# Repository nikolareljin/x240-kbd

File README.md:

# x240-kbd

A standalone USB keyboard with touchpad **and TrackPoint**, built from a ThinkPad X240
keyboard assembly (FRU 0C44020) and its Synaptics ClickPad, driven by a Raspberry Pi Pico
(RP2040) running QMK.

Works on **any OS without drivers** — it enumerates as a standard USB HID composite device
(keyboard + mouse + media keys).

> **Project status: design, not yet built.** The matrix pinout is unverified until the
> probing step runs on real hardware, and the TrackPoint route (via the ClickPad's PS/2
> pass-through) is the expected architecture, confirmed by the same step. Everything else
> here is designed to survive either answer. Track progress in the
> [issues](https://github.com/nikolareljin/x240-kbd/issues) — nine milestones from
> documentation to release.

---

## Features

- Full 84-key ThinkPad X240 layout (QWERTY, US)
- Synaptics ClickPad — cursor, left/right click zones
- **TrackPoint** — via the ClickPad's pass-through port, decoded in firmware
- FN layer with the ThinkPad media/system keys; FN Lock (FN + Esc)
- Keyboard backlight, 5 levels (backlit keyboard variants; no breathing — software PWM)
- Power button with a 500 ms long-press guard → OS power/sleep
- Touchpad indicator LED
- N-Key Rollover
- Micro-USB; documented USB-C upgrade
- Two enclosure routes: **3D-printed** (split case) or **hand-made with no printer**
- Two electronics revisions: **Rev A perfboard** and **Rev B KiCad PCB**, same firmware

---

## Hardware at a glance

| Component | Detail |
|---|---|
| Controller | Raspberry Pi Pico, RP2040, 26 GPIO |
| Keyboard | X240 0C44020, 40-pin 0.5 mm FPC; matrix size **measured by probing** |
| Sense expansion | 3 × 74HC165 shift registers — 24 sense lines on 3 GPIO |
| Touchpad + TrackPoint | Synaptics ClickPad, PS/2 on GP21/GP22 (RP2040 PIO driver) |
| Backlight | LED strip via 2N7002/BS170 MOSFET on GP26 |
| Power button | GP27, active LOW |
| USB | Micro-USB; USB-C via the Pico's TP1/TP2/TP3 pads |
| Enclosure | Printed split case, or the original X240 base cover, laser-cut plates, a Hammond console or wood |

Why a shift register: the closest documented ThinkPad keyboard of this era needs 26 matrix
lines — every GPIO the Pico has. [`docs/hardware/gpio-budget.md`](docs/hardware/gpio-budget.md).

### Cost

| Build | All-in (USD, Aug 2026) |
|---|---|
| Rev A + your own printer | **$90–130** |
| Rev A + reused X240 base cover, no printer | **$110–150** |
| Rev B PCB | add $25–35 |

The donor keyboard and palmrest are most of it. Full tiers and part links:
[`docs/hardware/bom-and-cost.md`](docs/hardware/bom-and-cost.md).

---

## Repository structure

```
x240-kbd/
├── firmware/qmk/keyboards/x240_pico/   QMK keyboard definition (corrected in milestone M4)
├── hardware/pinout/                     FPC pin maps — filled by probing
├── hardware/wiring/                     GPIO table (the single authoritative copy) and schematics
├── hardware/pcb/                        Rev B KiCad project (milestone M7)
├── tools/matrix_probe/                  CircuitPython matrix discovery
├── tools/ps2_sniffer/                   CircuitPython PS/2 + Synaptics sniffer
├── cad/                                 OpenSCAD: split case and small printed parts
└── docs/                                The documentation site (GitHub Pages from /docs)
    ├── hardware/                        components, BOM & cost, GPIO budget, sense chain, TrackPoint, backlight, PCB
    ├── firmware/                        architecture, QMK configuration, pointing stack
    ├── enclosure/                       printed, hand-made, integration, durability, presentation
    ├── references.md · glossary.md
    └── images/
```

---

## Quick start

Everything runs through one entry point, `./dev` (verbs from the workspace-wide
[script-helpers](https://github.com/nikolareljin/script-helpers) template; toolchains in
Docker, so the host needs only `docker`, `git` and `python3`):

```bash
./dev install            # submodules, docker images, a shallow qmk_firmware checkout
./dev build [firmware|docs|tools|cad|pcb|all]
./dev test               # host pytest for the tools, link check, shellcheck
./dev preflight          # everything CI runs: test + build all
./dev deploy             # copy the UF2 to the Pico's RPI-RP2 drive  (alias: ./flash)
./dev deploy matrix_probe   # copy a probing tool to CIRCUITPY        (alias: ./probe <tool>)
./dev devices            # RPI-RP2 / CIRCUITPY mounts and serial ports
./dev logs               # qmk console — the firmware's debug output
```

Shims `./build`, `./test`, `./flash`, `./probe`, `./site` wrap the same verbs. Artifacts
land in `out/`. The Docker images and the `qmk_firmware` commit are **pinned by digest**
in `scripts/toolchain.env` (`scripts/pull_toolchain.sh` pulls, saves or refreshes them),
so today's build can be repeated later. CI (`.github/workflows/ci.yml`, via
[ci-helpers](https://github.com/nikolareljin/ci-helpers)) runs `./dev test` and
`./dev build all` on every push and PR.

1. **Read the component reference and buy parts** —
   [`docs/hardware/components.md`](docs/hardware/components.md),
   [`docs/hardware/bom-and-cost.md`](docs/hardware/bom-and-cost.md).
2. **Probe the FPC pinouts — mandatory first step.** Flash CircuitPython, `./probe
   matrix_probe`, then `./probe ps2_sniffer`, following
   [`hardware/pinout/probing_procedure.md`](hardware/pinout/probing_procedure.md). Do not
   wire the Pico to anything before this is done.
3. **Build the Rev A adapter** — [`ASSEMBLY.md`](ASSEMBLY.md) Phase 2, using
   [`hardware/wiring/wiring_diagram.md`](hardware/wiring/wiring_diagram.md).
4. **Build and flash firmware** — `./dev build` then `./dev deploy` (hold BOOTSEL while
   plugging in). Without `./dev`: copy `firmware/qmk/keyboards/x240_pico` into a QMK
   checkout and `qmk compile -kb x240_pico -km default`. The firmware **builds** (custom
   74HC165 matrix, PIO PS/2 host, Synaptics + TrackPoint decoding); the key map is a
   placeholder until probing (#38). [`docs/firmware/qmk-configuration.md`](docs/firmware/qmk-configuration.md).
5. **Choose an enclosure** — printed:
   [`docs/enclosure/printed.md`](docs/enclosure/printed.md); no printer:
   [`docs/enclosure/handmade.md`](docs/enclosure/handmade.md).
6. **Close it up** — [`docs/enclosure/presentation.md`](docs/enclosure/presentation.md)
   has the assembly order.

---

## FN key map

| FN + | Action | | FN + | Action |
|---|---|---|---|---|
| F1 | Mute | | F9 | Settings |
| F2 | Volume down | | F10 | Bluetooth |
| F3 | Volume up | | F11 | **Backlight step** |
| F4 | Mic mute (F20) | | F12 | Print Screen |
| F5 | Brightness down | | PgUp / PgDn | Home / End |
| F6 | Brightness up | | Left / Right | Previous / next track |
| F7 | External display | | Esc | **FN Lock** |
| F8 | Wireless toggle | | | |

---

## USB-C upgrade (optional)

Wire a USB-C female breakout (one with 5.1 kΩ CC pull-downs) to the pads on the Pico's
underside:

| Pico pad | Signal | Breakout |
|---|---|---|
| **TP1** | **GND** | GND |
| **TP2** | **USB D−** | D− |
| **TP3** | **USB D+** | D+ |
| VBUS (pin 40) | 5 V | VBUS |

Set `usb_c = true` in `cad/bottom_case.scad` for the USB-C cutout. No firmware change.

> The illustration [`docs/images/usb_c_wiring.png`](docs/images/usb_c_wiring.png) is
> decorative; its pad labels predate this table and are **not** the wiring reference.
> Source: [Pico datasheet, test points](https://datasheets.raspberrypi.com/pico/pico-datasheet.pdf).

Alternatively use a **Pimoroni Pico LiPo** (USB-C native, same pinout).

---

## Flashing

- **First flash:** hold BOOTSEL while plugging in → `RPI-RP2` drive → drag the `.uf2`.
- **After that:** `./dev deploy`, or hold the top-left key (Esc) while plugging in (Bootmagic).
- **Recommended:** wire a tactile switch to the Pico's `RUN` pad, reachable through the
  case, so BOOTSEL + reset works without opening anything.

---

## Documentation

The site is built from `docs/` (GitHub Pages, milestone M1). Start at
[`docs/README.md`](docs/README.md). Builder guides: [`ASSEMBLY.md`](ASSEMBLY.md),
[`PLAN.md`](PLAN.md). Changes: [`CHANGELOG.md`](CHANGELOG.md).

## References

Annotated list in [`docs/references.md`](docs/references.md). The projects this one stands
on: [delingren/thinkpad_keyboards](https://github.com/delingren/thinkpad_keyboards),
[hamishcoleman/thinkpad-usbkb](https://github.com/hamishcoleman/thinkpad-usbkb),
[thedalles77/USB_Laptop_Keyboard_Controller](https://github.com/thedalles77/USB_Laptop_Keyboard_Controller).

## Repository

[nikolareljin/x240-kbd](https://github.com/nikolareljin/x240-kbd) · GPL-2.0, matching QMK.

## Clone traffic

_Updated daily. Total and unique cloners over the last 14 days._

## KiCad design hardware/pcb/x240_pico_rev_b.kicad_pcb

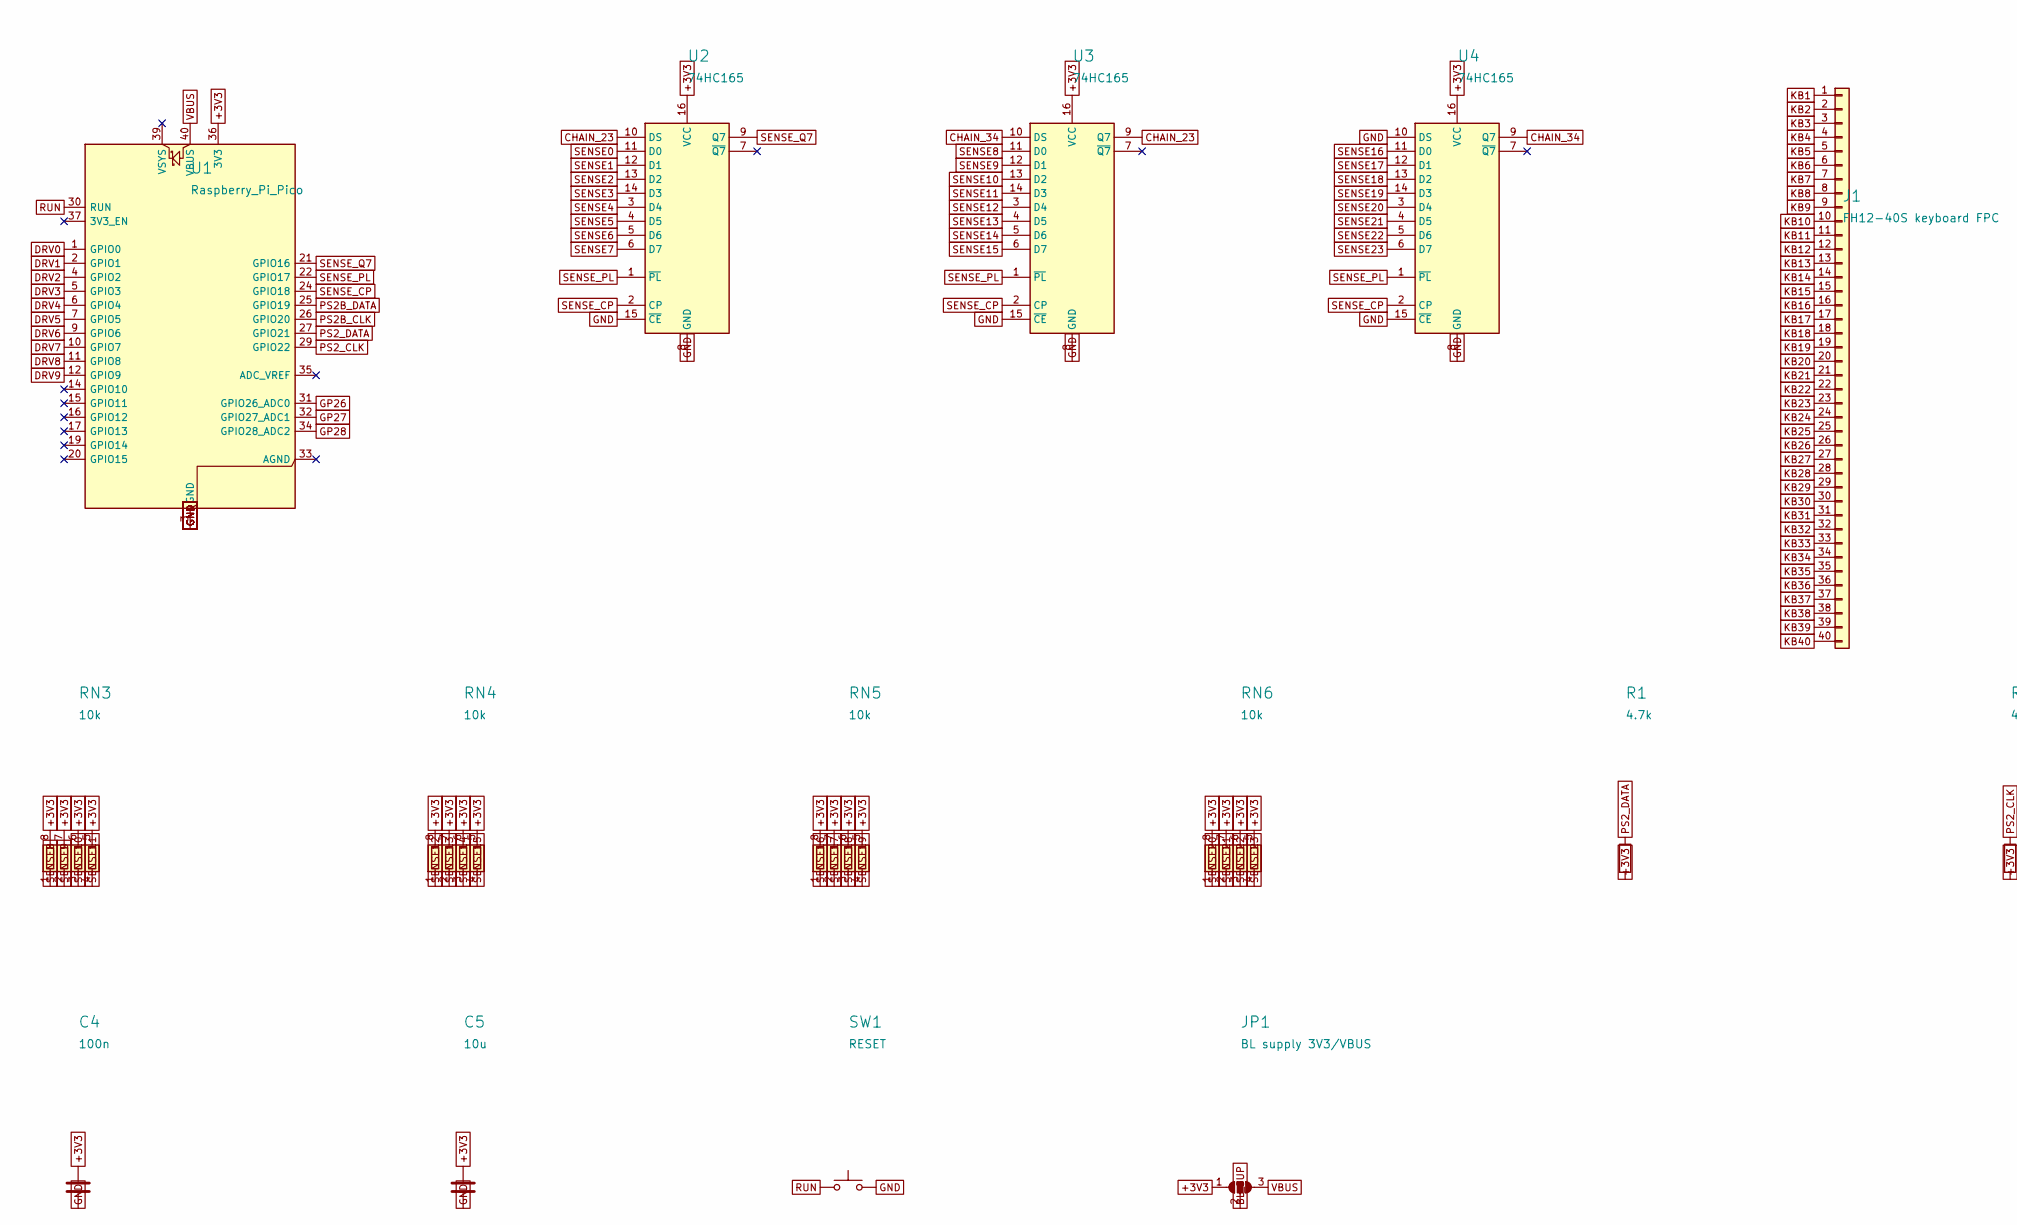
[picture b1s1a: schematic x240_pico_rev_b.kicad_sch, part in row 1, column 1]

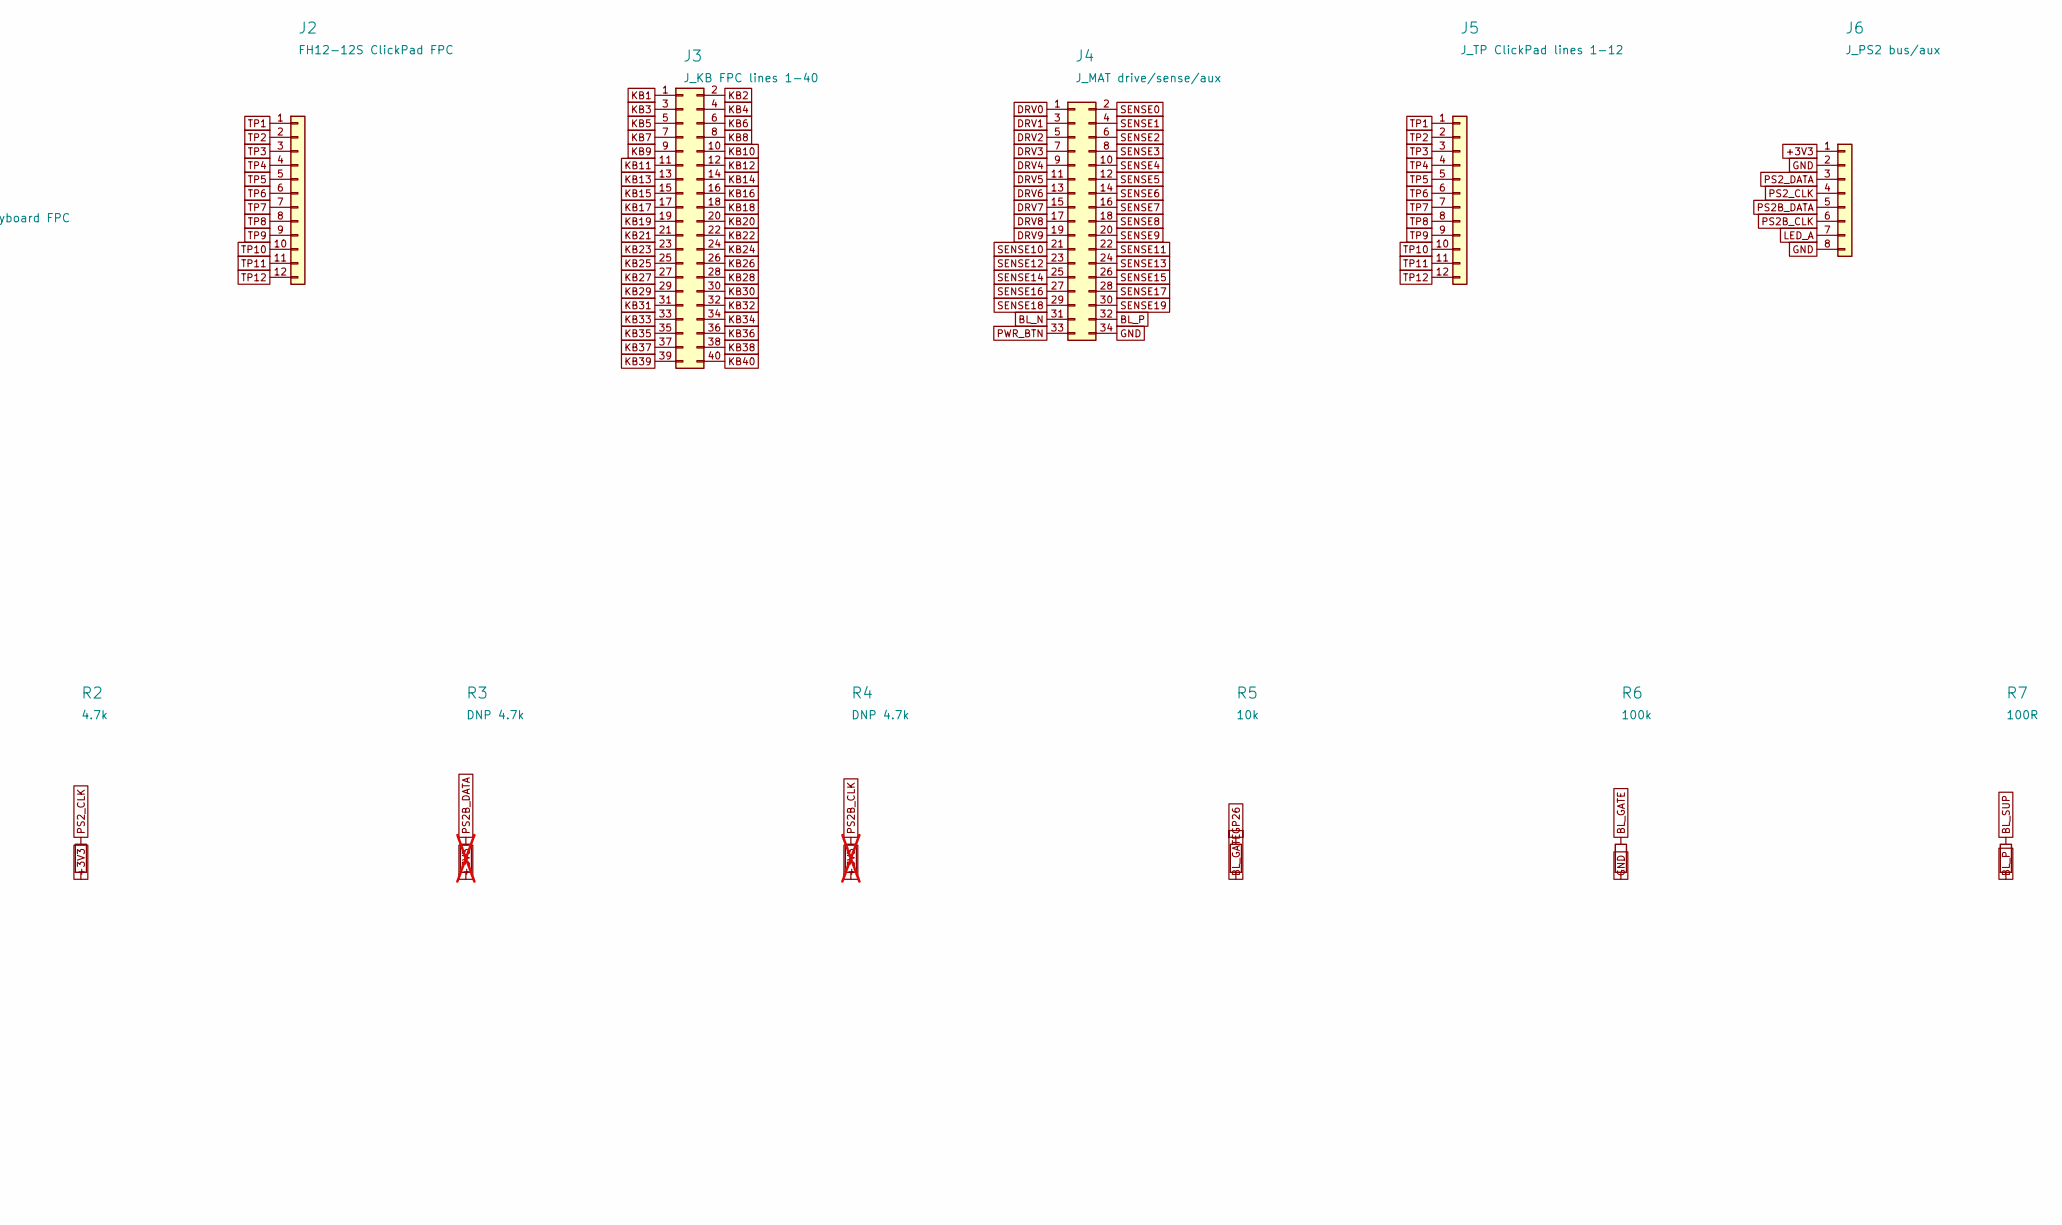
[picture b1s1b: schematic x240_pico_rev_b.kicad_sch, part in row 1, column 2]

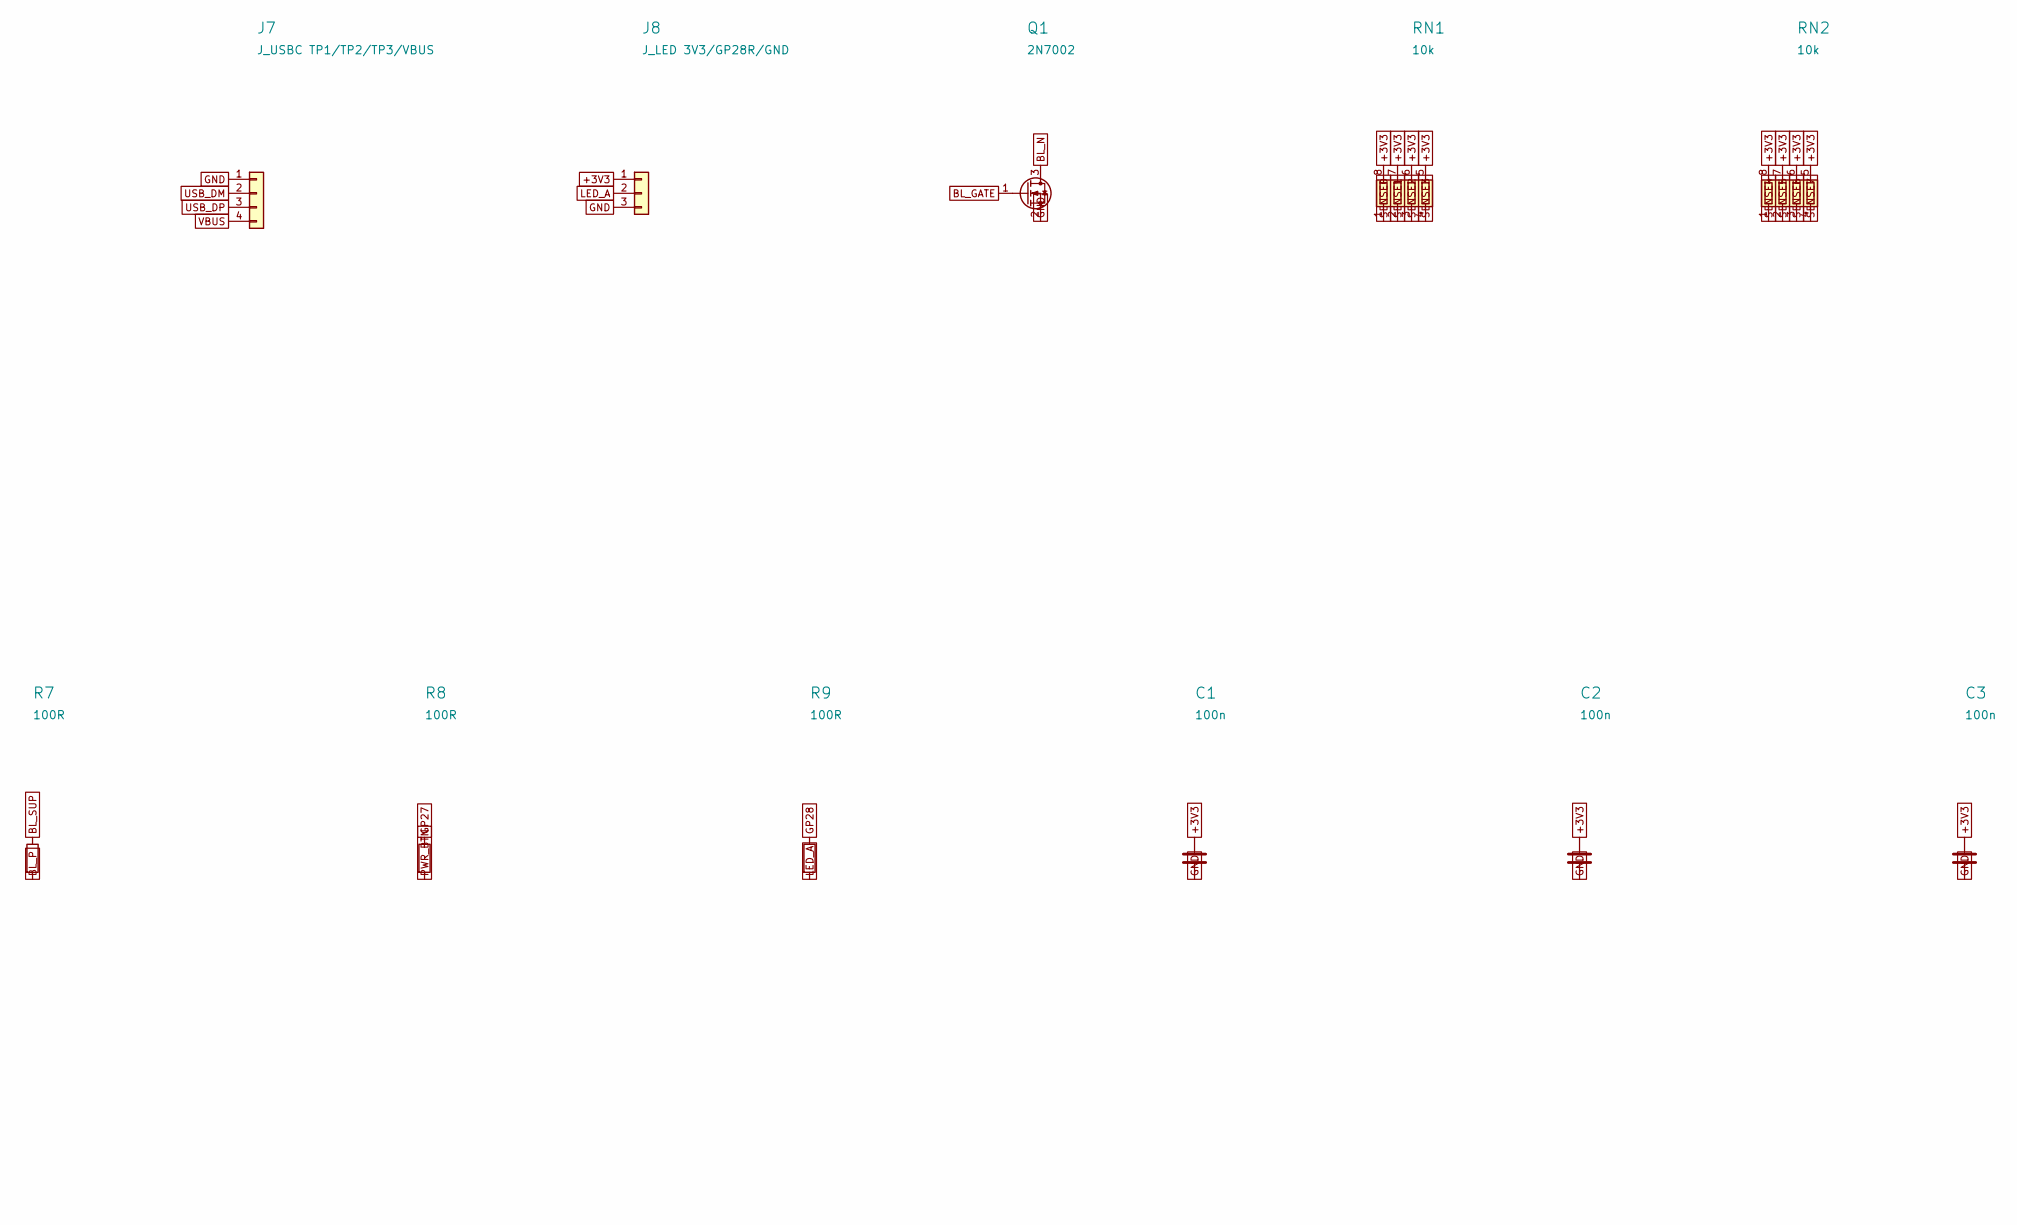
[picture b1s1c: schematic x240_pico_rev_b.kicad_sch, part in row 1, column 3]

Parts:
C1, C2, C3, C4: 100n; C_0603_1608Metric
C5: 10u; C_0805_2012Metric
J1: FH12-40S keyboard FPC; Hirose_FH12-40S-0.5SH_1x40-1MP_P0.50mm_Horizontal
J2: FH12-12S ClickPad FPC; Hirose_FH12-12S-0.5SH_1x12-1MP_P0.50mm_Horizontal
J3: J_KB FPC lines 1-40; PinHeader_2x20_P2.54mm_Vertical
J4: J_MAT drive/sense/aux; PinHeader_2x17_P2.54mm_Vertical
J5: J_TP ClickPad lines 1-12; PinHeader_1x12_P2.54mm_Vertical
J6: J_PS2 bus/aux; PinHeader_1x08_P2.54mm_Vertical
J7: J_USBC TP1/TP2/TP3/VBUS; PinHeader_1x04_P2.54mm_Vertical
J8: J_LED 3V3/GP28R/GND; PinHeader_1x03_P2.54mm_Vertical
JP1: BL supply 3V3/VBUS; SolderJumper-3_P1.3mm_Open_RoundedPad1.0x1.5mm
Q1: 2N7002; SOT-23
R1, R2: 4.7k; R_0603_1608Metric
R3, R4: DNP 4.7k; R_0603_1608Metric; not fitted
R5: 10k; R_0603_1608Metric
R6: 100k; R_0603_1608Metric
R7, R8, R9: 100R; R_0603_1608Metric
RN1, RN2, RN3, RN4, RN5, RN6: 10k; R_Array_Convex_4x0603
SW1: RESET; SW_PUSH_6mm
U1: Raspberry_Pi_Pico; RaspberryPi_Pico_Common_THT
U2, U3, U4: 74HC165; TSSOP-16_4.4x5mm_P0.65mm

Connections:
+3V3: C1.1, C2.1, C3.1, C4.1, C5.1, J6.1, J8.1, JP1.1 (A), R1.2, R2.2, R3.2, R4.2, RN1.5 (R4.2), RN1.6 (R3.2), RN1.7 (R2.2), RN1.8 (R1.2), RN2.5 (R4.2), RN2.6 (R3.2), RN2.7 (R2.2), RN2.8 (R1.2), RN3.5 (R4.2), RN3.6 (R3.2), RN3.7 (R2.2), RN3.8 (R1.2), RN4.5 (R4.2), RN4.6 (R3.2), RN4.7 (R2.2), RN4.8 (R1.2), RN5.5 (R4.2), RN5.6 (R3.2), RN5.7 (R2.2), RN5.8 (R1.2), RN6.5 (R4.2), RN6.6 (R3.2), RN6.7 (R2.2), RN6.8 (R1.2), U1.36 (3V3), U2.16 (VCC), U3.16 (VCC), U4.16 (VCC)
BL_GATE: Q1.1 (G), R5.2, R6.1
BL_N: J4.31, Q1.3 (D)
BL_P: J4.32, R7.2
BL_SUP: JP1.2 (C), R7.1
CHAIN_23: U2.10 (DS), U3.9 (Q7)
CHAIN_34: U3.10 (DS), U4.9 (Q7)
DRV0: J4.1, U1.1 (GPIO0)
DRV1: J4.3, U1.2 (GPIO1)
DRV2: J4.5, U1.4 (GPIO2)
DRV3: J4.7, U1.5 (GPIO3)
DRV4: J4.9, U1.6 (GPIO4)
DRV5: J4.11, U1.7 (GPIO5)
DRV6: J4.13, U1.9 (GPIO6)
DRV7: J4.15, U1.10 (GPIO7)
DRV8: J4.17, U1.11 (GPIO8)
DRV9: J4.19, U1.12 (GPIO9)
GND: C1.2, C2.2, C3.2, C4.2, C5.2, J4.34, J6.2, J6.8, J7.1, J8.3, Q1.2 (S), R6.2, SW1.2, U1.3 (GND), U1.8 (GND), U1.13 (GND), U1.18 (GND), U1.23 (GND), U1.28 (GND), U1.38 (GND), U2.8 (GND), U2.15 (~CE), U3.8 (GND), U3.15 (~CE), U4.8 (GND), U4.10 (DS), U4.15 (~CE)
GP26: R5.1, U1.31 (GPIO26_ADC0)
GP27: R8.1, U1.32 (GPIO27_ADC1)
GP28: R9.1, U1.34 (GPIO28_ADC2)
KB1: J1.1, J3.1
KB2: J1.2, J3.2
KB3: J1.3, J3.3
KB4: J1.4, J3.4
KB5: J1.5, J3.5
KB6: J1.6, J3.6
KB7: J1.7, J3.7
KB8: J1.8, J3.8
KB9: J1.9, J3.9
KB10: J1.10, J3.10
KB11: J1.11, J3.11
KB12: J1.12, J3.12
KB13: J1.13, J3.13
KB14: J1.14, J3.14
KB15: J1.15, J3.15
KB16: J1.16, J3.16
KB17: J1.17, J3.17
KB18: J1.18, J3.18
KB19: J1.19, J3.19
KB20: J1.20, J3.20
KB21: J1.21, J3.21
KB22: J1.22, J3.22
KB23: J1.23, J3.23
KB24: J1.24, J3.24
KB25: J1.25, J3.25
KB26: J1.26, J3.26
KB27: J1.27, J3.27
KB28: J1.28, J3.28
KB29: J1.29, J3.29
KB30: J1.30, J3.30
KB31: J1.31, J3.31
KB32: J1.32, J3.32
KB33: J1.33, J3.33
KB34: J1.34, J3.34
KB35: J1.35, J3.35
KB36: J1.36, J3.36
KB37: J1.37, J3.37
KB38: J1.38, J3.38
KB39: J1.39, J3.39
KB40: J1.40, J3.40
LED_A: J6.7, J8.2, R9.2
PS2B_CLK: J6.6, R4.1, U1.26 (GPIO20)
PS2B_DATA: J6.5, R3.1, U1.25 (GPIO19)
PS2_CLK: J6.4, R2.1, U1.29 (GPIO22)
PS2_DATA: J6.3, R1.1, U1.27 (GPIO21)
PWR_BTN: J4.33, R8.2
RUN: SW1.1, U1.30 (RUN)
SENSE0: J4.2, RN1.1 (R1.1), U2.11 (D0)
SENSE1: J4.4, RN1.2 (R2.1), U2.12 (D1)
SENSE2: J4.6, RN1.3 (R3.1), U2.13 (D2)
SENSE3: J4.8, RN1.4 (R4.1), U2.14 (D3)
SENSE4: J4.10, RN2.1 (R1.1), U2.3 (D4)
SENSE5: J4.12, RN2.2 (R2.1), U2.4 (D5)
SENSE6: J4.14, RN2.3 (R3.1), U2.5 (D6)
SENSE7: J4.16, RN2.4 (R4.1), U2.6 (D7)
SENSE8: J4.18, RN3.1 (R1.1), U3.11 (D0)
SENSE9: J4.20, RN3.2 (R2.1), U3.12 (D1)
SENSE10: J4.21, RN3.3 (R3.1), U3.13 (D2)
SENSE11: J4.22, RN3.4 (R4.1), U3.14 (D3)
SENSE12: J4.23, RN4.1 (R1.1), U3.3 (D4)
SENSE13: J4.24, RN4.2 (R2.1), U3.4 (D5)
SENSE14: J4.25, RN4.3 (R3.1), U3.5 (D6)
SENSE15: J4.26, RN4.4 (R4.1), U3.6 (D7)
SENSE16: J4.27, RN5.1 (R1.1), U4.11 (D0)
SENSE17: J4.28, RN5.2 (R2.1), U4.12 (D1)
SENSE18: J4.29, RN5.3 (R3.1), U4.13 (D2)
SENSE19: J4.30, RN5.4 (R4.1), U4.14 (D3)
SENSE20: RN6.1 (R1.1), U4.3 (D4)
SENSE21: RN6.2 (R2.1), U4.4 (D5)
SENSE22: RN6.3 (R3.1), U4.5 (D6)
SENSE23: RN6.4 (R4.1), U4.6 (D7)
SENSE_CP: U1.24 (GPIO18), U2.2 (CP), U3.2 (CP), U4.2 (CP)
SENSE_PL: U1.22 (GPIO17), U2.1 (~PL), U3.1 (~PL), U4.1 (~PL)
SENSE_Q7: U1.21 (GPIO16), U2.9 (Q7)
TP1: J2.1, J5.1
TP2: J2.2, J5.2
TP3: J2.3, J5.3
TP4: J2.4, J5.4
TP5: J2.5, J5.5
TP6: J2.6, J5.6
TP7: J2.7, J5.7
TP8: J2.8, J5.8
TP9: J2.9, J5.9
TP10: J2.10, J5.10
TP11: J2.11, J5.11
TP12: J2.12, J5.12
USB_DM: J7.2
USB_DP: J7.3
VBUS: J7.4, JP1.3 (B), U1.40 (VBUS)

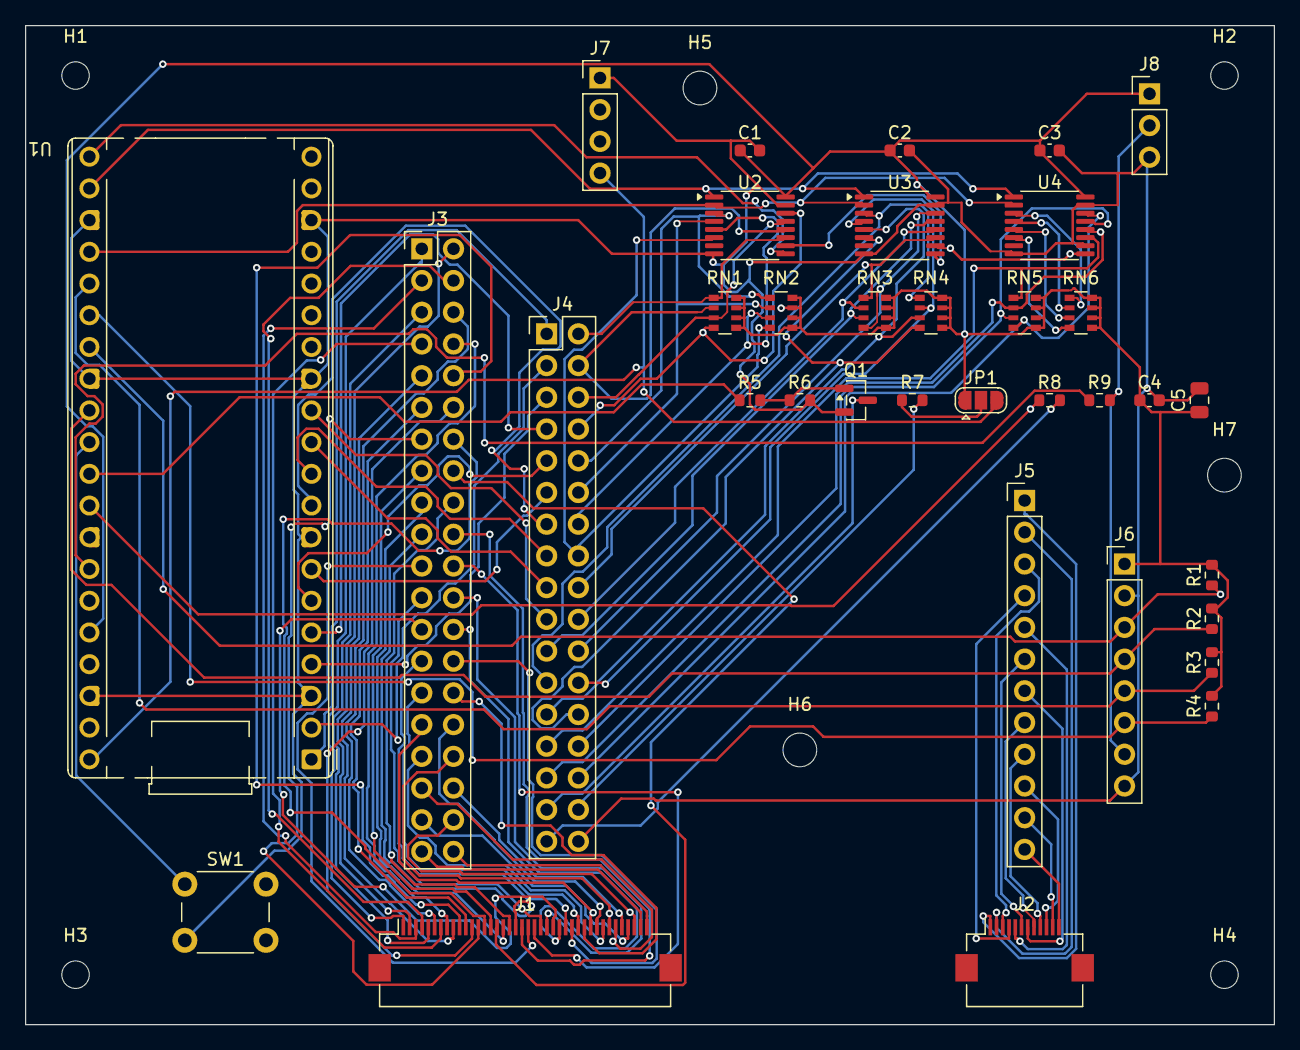
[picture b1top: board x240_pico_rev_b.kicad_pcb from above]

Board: 2 copper layers, 100.0 x 80.0 mm, 42 parts (0 on the bottom side), 108 nets.

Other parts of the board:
H1, H2, H3, H4: MountingHole_2.2mm_M2
H5, H6, H7: MountingHole_2.7mm_M2.5

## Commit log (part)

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2026-04-07 Initial public x240-kbd project
2026-04-07 chore: separate agents instructions from local memory
2026-04-07 fix: poll dedicated power button input
2026-06-18 docs: add clone traffic chart
